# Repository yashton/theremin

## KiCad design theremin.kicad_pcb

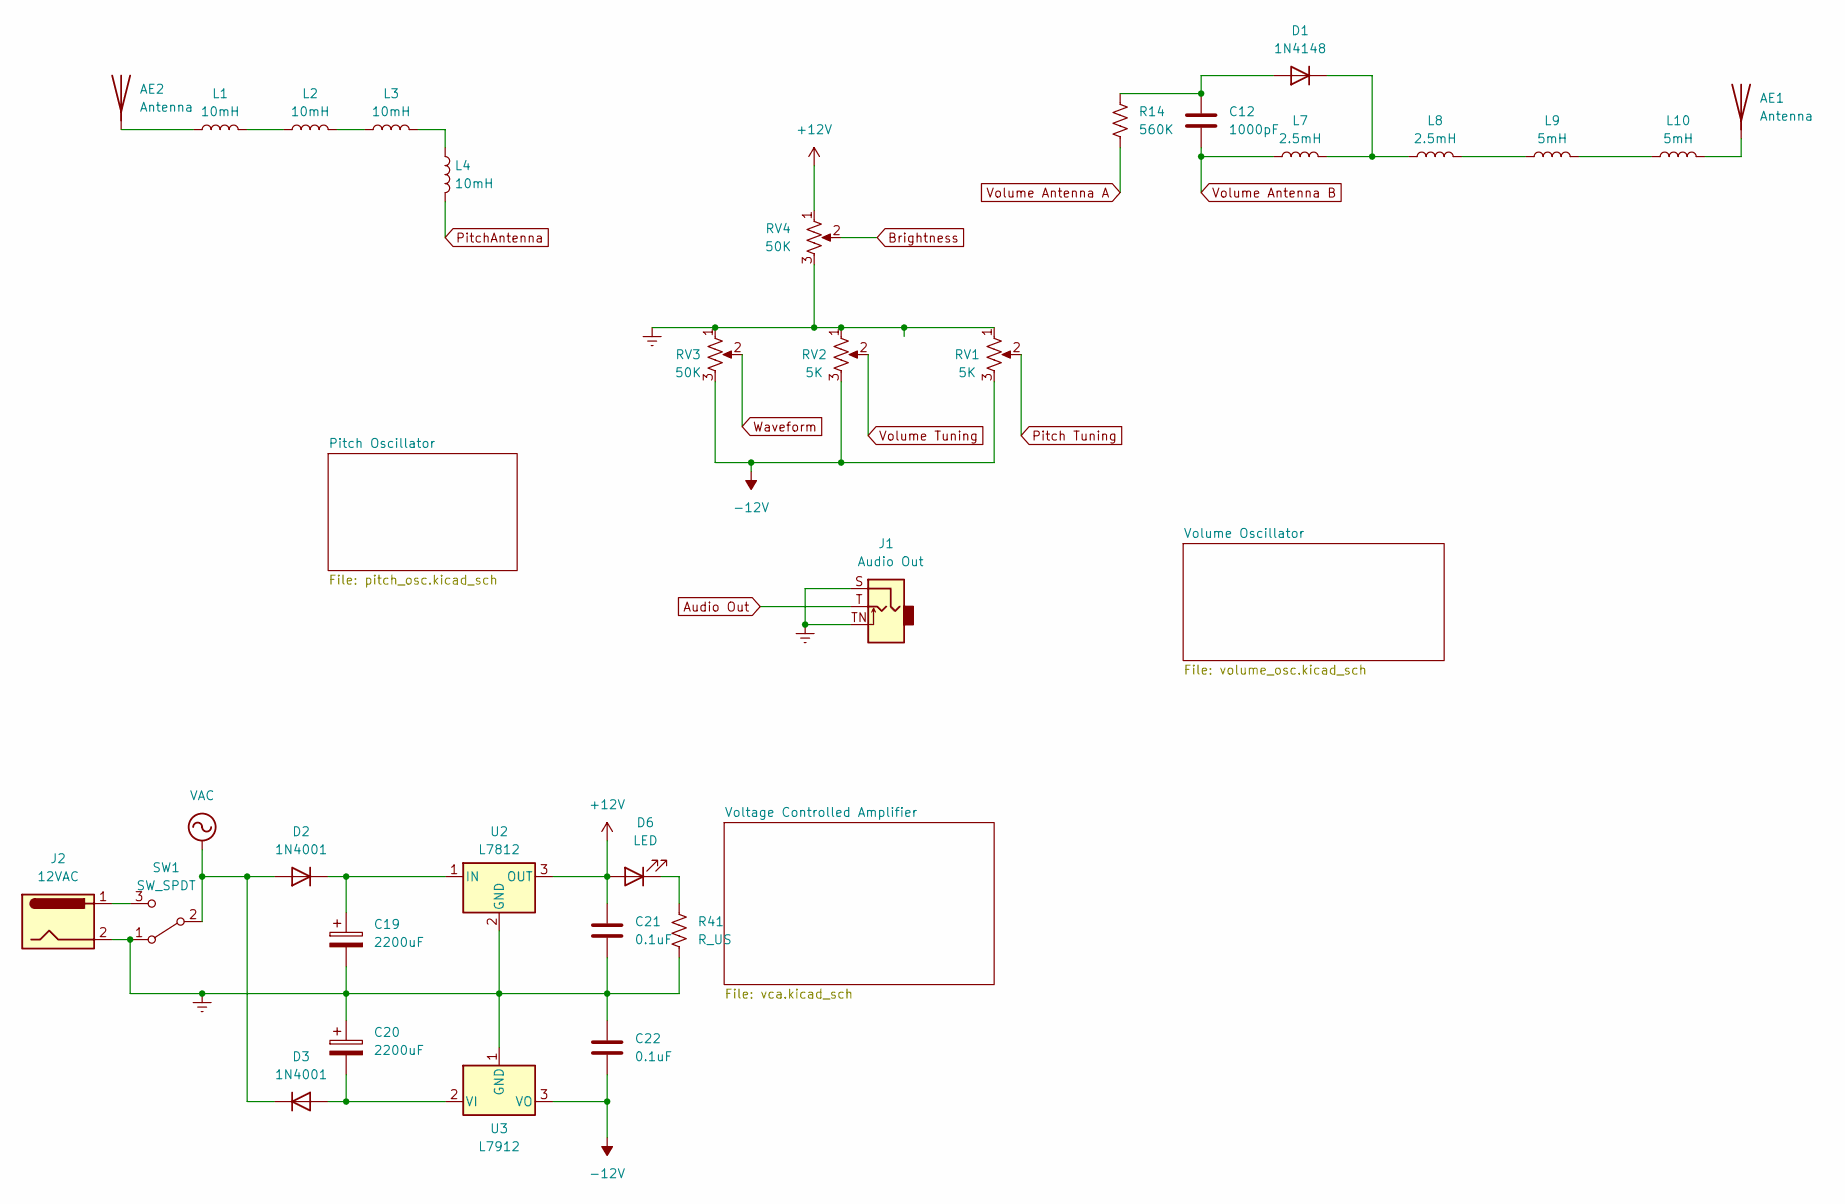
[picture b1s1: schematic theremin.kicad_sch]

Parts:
AE1, AE2: Antenna; Pin_D1.3mm_L11.0mm
C12: 1000pF; C_0805_2012Metric
C19, C20: 2200uF; CP_Radial_D10.0mm_P3.50mm
C21, C22: 0.1uF; C_1812_4532Metric
D1: 1N4148; D_2010_5025Metric
D2, D3: 1N4001; D_2010_5025Metric
D6: LED; LED_D3.0mm_Horizontal_O1.27mm_Z2.0mm_IRGrey
J1: Audio Out; Jack_3.5mm_CUI_SJ1-3533NG_Horizontal
J2: 12VAC; BarrelJack_CUI_PJ-063AH_Horizontal
L1, L2, L3, L4: 10mH; L_1210_3225Metric
L7, L8: 2.5mH; L_1210_3225Metric
L9, L10: 5mH; L_1210_3225Metric
R14: 560K; R_0805_2012Metric
R41: R_US; R_0805_2012Metric
RV1, RV2: 5K; Potentiometer_Vishay_148-149_Single_Horizontal
RV3, RV4: 50K; Potentiometer_Vishay_148-149_Single_Horizontal
SW1: SW_SPDT; SW_Push_1P2T_Vertical_E-Switch_800UDP8P1A1M6
U2: L7812; TO-220-3_Vertical
U3: L7912; TO-220-3_Vertical

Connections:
+12V: C21.1, D6.2 (A), RV4.1, U2.3 (OUT); also elsewhere on the board
-12V: C22.2, RV1.3, RV2.3, RV3.3, U3.3 (VO); also elsewhere on the board
Audio Out: J1.T; also elsewhere on the board
Brightness: RV4.2; also elsewhere on the board
Earth: C19.2, C20.1, C21.2, C22.1, J1.S, J1.TN, J2.2, R41.1, RV1.1, RV2.1, RV3.1, RV4.3, SW1.1 (A), U2.2 (GND), U3.1 (GND); also elsewhere on the board
unnamed: AE1.1 (A), L10.2
unnamed: AE2.1 (A), L1.1
unnamed: C12.1, D1.2 (A), R14.1
unnamed: D1.1 (K), L7.2, L8.1
unnamed: C19.1, D2.1 (K), U2.1 (IN)
unnamed: C20.2, D3.2 (A), U3.2 (VI)
unnamed: D6.1 (K), R41.2
unnamed: L1.2, L2.1
unnamed: L2.2, L3.1
unnamed: L3.2, L4.1
unnamed: L8.2, L9.1
unnamed: L9.2, L10.1
unnamed: J2.1, SW1.3 (C)
Pitch Tuning: RV1.2; also elsewhere on the board
PitchAntenna: L4.2; also elsewhere on the board
VAC: D2.2 (A), D3.1 (K), SW1.2 (B)
Volume Antenna A: R14.2; also elsewhere on the board
Volume Antenna B: C12.2, L7.1; also elsewhere on the board
Volume Tuning: RV2.2; also elsewhere on the board
Waveform: RV3.2; also elsewhere on the board

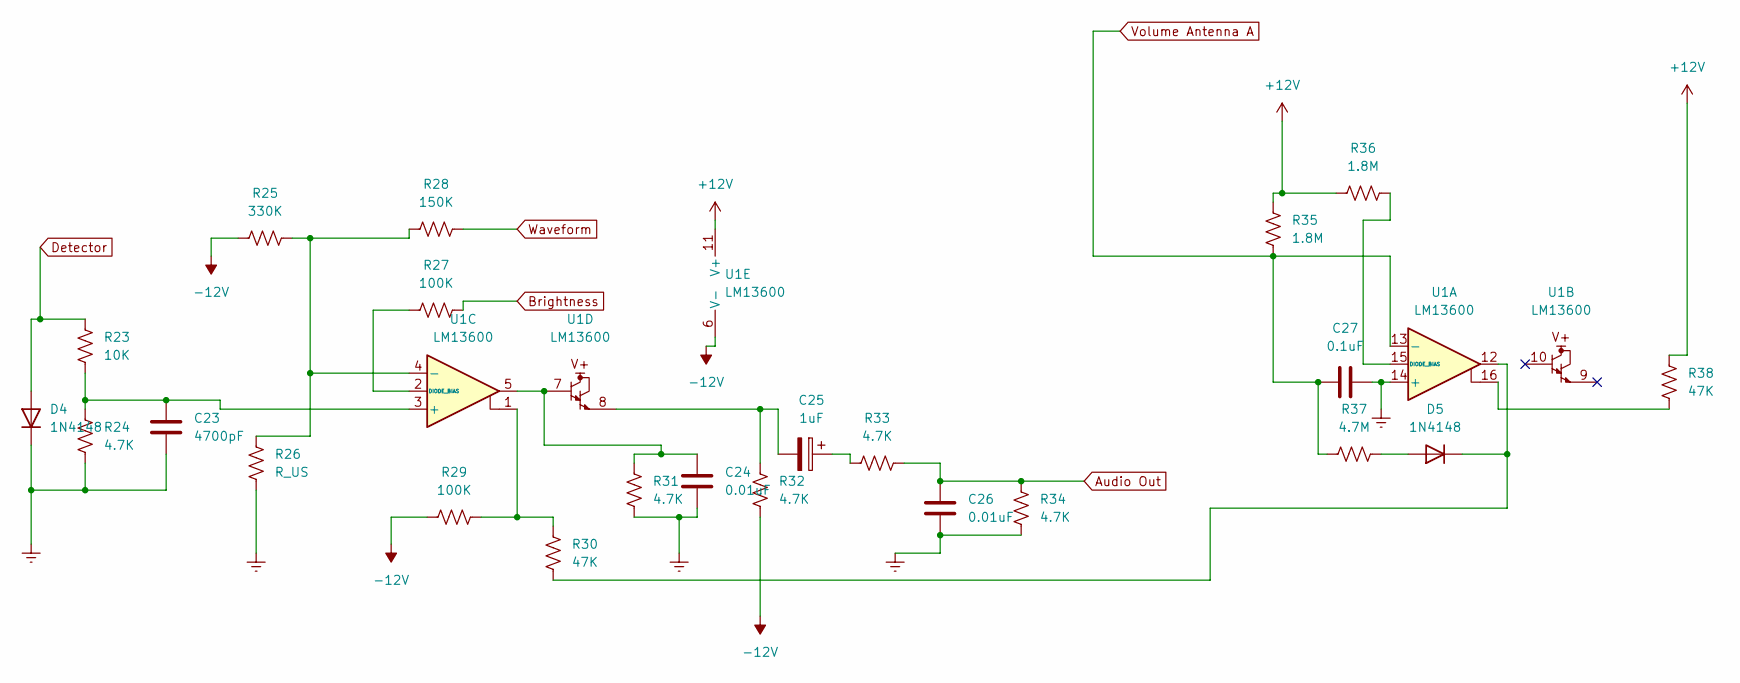
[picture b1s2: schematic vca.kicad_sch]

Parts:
C23: 4700pF; C_1812_4532Metric
C24, C26: 0.01uF; C_0805_2012Metric
C25: 1uF; CP_Radial_D5.0mm_P2.50mm
C27: 0.1uF; C_1812_4532Metric
D4, D5: 1N4148; D_2010_5025Metric
R23: 10K; R_0805_2012Metric
R24, R31, R32, R33, R34: 4.7K; R_0805_2012Metric
R25: 330K; R_0805_2012Metric
R26: R_US; R_0805_2012Metric
R27, R29: 100K; R_0805_2012Metric
R28: 150K; R_0805_2012Metric
R30, R38: 47K; R_0805_2012Metric
R35, R36: 1.8M; R_0805_2012Metric
R37: 4.7M; R_0805_2012Metric
U1: LM13600; DIP-16_W7.62mm_LongPads

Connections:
+12V: R35.2, R36.2, R38.1, U1.11 (V+); also elsewhere on the board
-12V: R25.1, R29.2, R32.2, U1.6 (V-); also elsewhere on the board
Audio Out: C26.1, R33.2, R34.2; also elsewhere on the board
Brightness: R27.1; also elsewhere on the board
Detector: D4.2 (A), R23.1; also elsewhere on the board
Earth: C23.2, C24.2, C26.2, C27.2, D4.1 (K), R24.2, R26.1, R31.2, R34.1, U1.14 (+); also elsewhere on the board
unnamed: C24.1, R31.1, U1.5, U1.7
unnamed: C25.1, R33.1
unnamed: C25.2, R32.1, U1.8
unnamed: D5.2 (A), R37.1
unnamed: D5.1 (K), R30.2, U1.12
unnamed: R29.1, R30.1, U1.1
unnamed: R38.2, U1.16
unnamed: R36.1, U1.15 (DIODE_BIAS)
unnamed: C23.1, R23.2, R24.1, U1.3 (+)
unnamed: R25.2, R26.2, R28.2, U1.4 (-)
unnamed: R27.2, U1.2 (DIODE_BIAS)
Volume Antenna A: C27.1, R35.1, R37.2, U1.13 (-); also elsewhere on the board
Waveform: R28.1; also elsewhere on the board

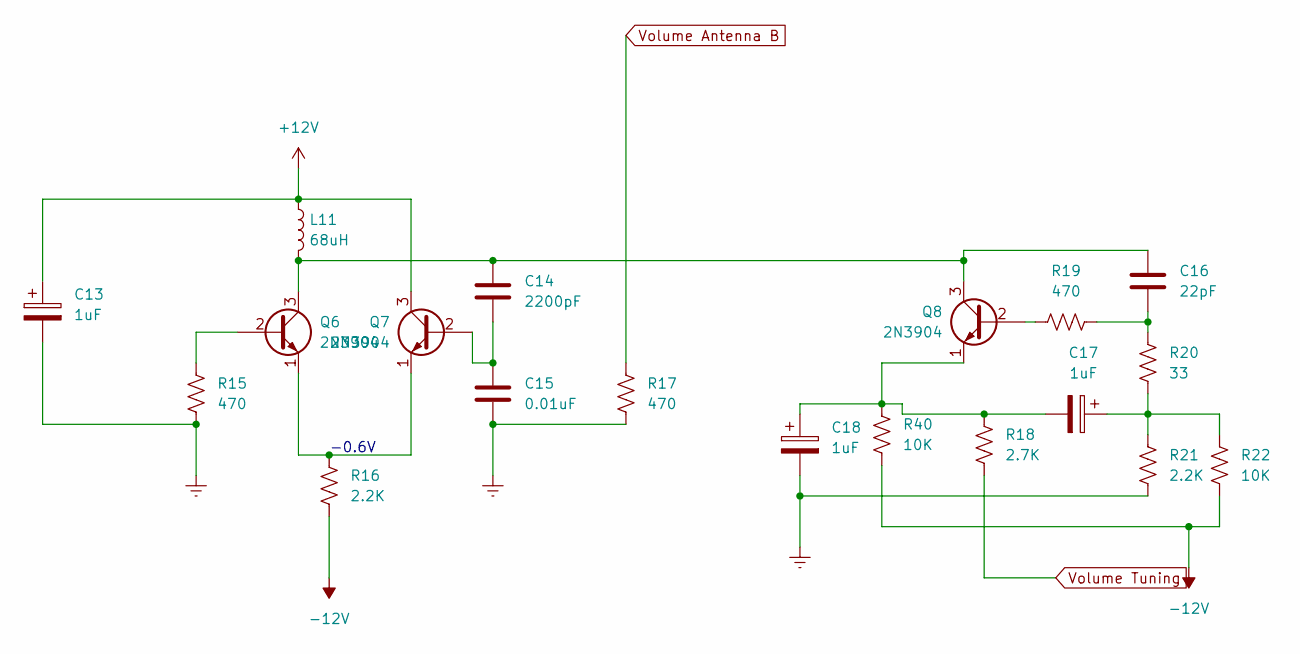
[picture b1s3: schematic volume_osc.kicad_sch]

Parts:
C13, C17, C18: 1uF; CP_Radial_D5.0mm_P2.50mm
C14: 2200pF; C_0805_2012Metric
C15: 0.01uF; C_0805_2012Metric
C16: 22pF; C_0805_2012Metric
L11: 68uH; L_1210_3225Metric
Q6, Q7, Q8: 2N3904; TO-92_Inline
R15, R17, R19: 470; R_0805_2012Metric
R16, R21: 2.2K; R_0805_2012Metric
R18: 2.7K; R_0805_2012Metric
R20: 33; R_0805_2012Metric
R22, R40: 10K; R_0805_2012Metric

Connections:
+12V: C13.1, L11.1, Q7.3 (C); also elsewhere on the board
-12V: R16.2, R22.1, R40.2; also elsewhere on the board
Earth: C13.2, C15.2, C18.2, R15.2, R17.2, R21.1; also elsewhere on the board
unnamed: C16.2, R19.2, R20.2
unnamed: C17.1, R20.1, R21.2, R22.2
unnamed: Q6.2 (B), R15.1
unnamed: C14.1, C16.1, L11.2, Q6.3 (C), Q8.3 (C)
unnamed: Q6.1 (E), Q7.1 (E), R16.1
unnamed: C14.2, C15.1, Q7.2 (B)
unnamed: Q8.2 (B), R19.1
unnamed: C17.2, C18.1, Q8.1 (E), R18.1, R40.1
Volume Antenna B: R17.1; also elsewhere on the board
Volume Tuning: R18.2; also elsewhere on the board

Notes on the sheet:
-0.6V

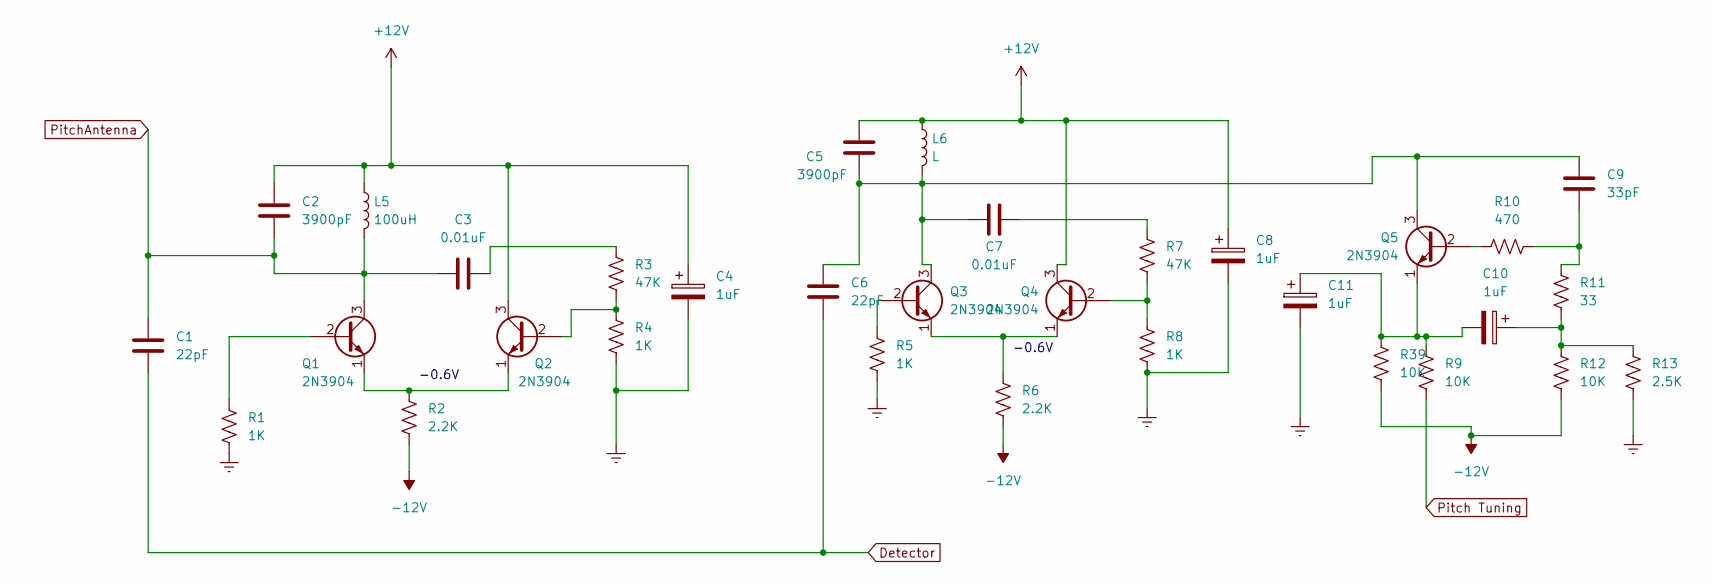
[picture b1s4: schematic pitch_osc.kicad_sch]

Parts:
C1, C6: 22pF; C_0805_2012Metric
C2, C5: 3900pF; C_0805_2012Metric
C3, C7: 0.01uF; C_0805_2012Metric
C4, C8, C10, C11: 1uF; CP_Radial_D5.0mm_P2.50mm
C9: 33pF; C_0805_2012Metric
L5: 100uH; L_1210_3225Metric
L6: L; L_1210_3225Metric
Q1, Q2, Q3, Q4, Q5: 2N3904; TO-92_Inline
R1, R4, R5, R8: 1K; R_0805_2012Metric
R2, R6: 2.2K; R_0805_2012Metric
R3, R7: 47K; R_0805_2012Metric
R9, R12, R39: 10K; R_0805_2012Metric
R10: 470; R_0805_2012Metric
R11: 33; R_0805_2012Metric
R13: 2.5K; R_0805_2012Metric

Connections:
+12V: C2.1, C4.1, C5.1, C8.1, L5.1, L6.1, Q2.3 (C), Q4.3 (C); also elsewhere on the board
-12V: R2.2, R6.2, R12.1, R39.2; also elsewhere on the board
Detector: C1.2, C6.2; also elsewhere on the board
Earth: C4.2, C8.2, C11.2, R1.2, R4.2, R5.2, R8.2, R13.1; also elsewhere on the board
unnamed: C3.2, R3.1
unnamed: C7.2, R7.1
unnamed: C9.1, R10.2, R11.2
unnamed: C10.1, R11.1, R12.2, R13.2
unnamed: Q1.2 (B), R1.1
unnamed: Q1.1 (E), Q2.1 (E), R2.1
unnamed: Q2.2 (B), R3.2, R4.1
unnamed: Q3.2 (B), R5.1
unnamed: C5.2, C6.1, C7.1, C9.2, L6.2, Q3.3 (C), Q5.3 (C)
unnamed: Q3.1 (E), Q4.1 (E), R6.1
unnamed: Q4.2 (B), R7.2, R8.1
unnamed: Q5.2 (B), R10.1
unnamed: C10.2, C11.1, Q5.1 (E), R9.1, R39.1
Pitch Tuning: R9.2; also elsewhere on the board
PitchAntenna: C1.1, C2.2, C3.1, L5.2, Q1.3 (C); also elsewhere on the board

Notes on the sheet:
-0.6V

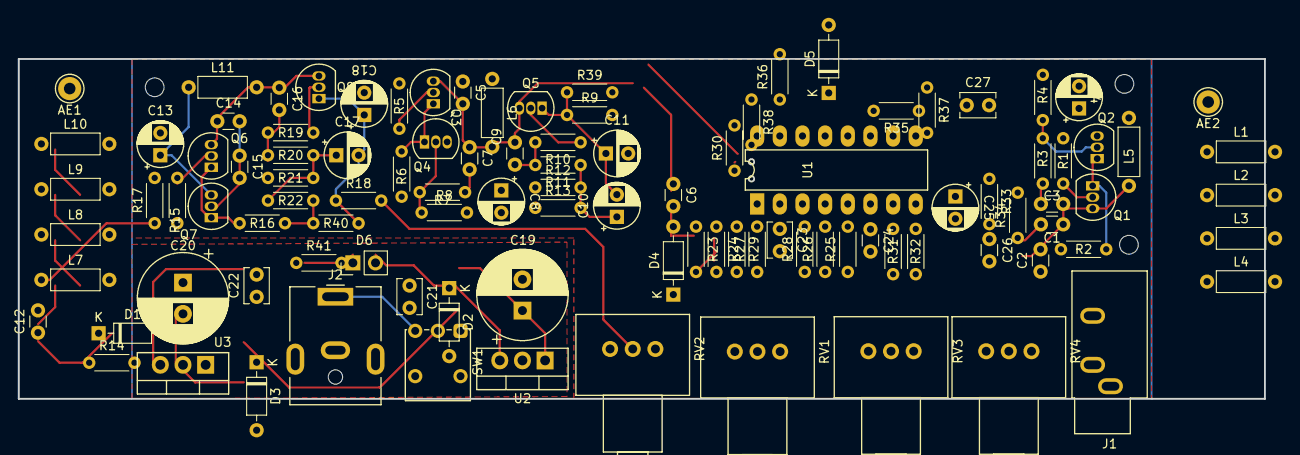
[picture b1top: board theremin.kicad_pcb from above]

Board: 2 copper layers, 139.7 x 38.1 mm, 105 parts (0 on the bottom side), 58 nets.

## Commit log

2024-01-24 Initial schematic copied from Moog article.
2024-01-24 Initial placement for pcb.
2024-01-25 Placed in smd and through.
2024-01-25 Layout cleanup for smd and through
2024-01-25 Small update
2024-01-26 Finished VPO
